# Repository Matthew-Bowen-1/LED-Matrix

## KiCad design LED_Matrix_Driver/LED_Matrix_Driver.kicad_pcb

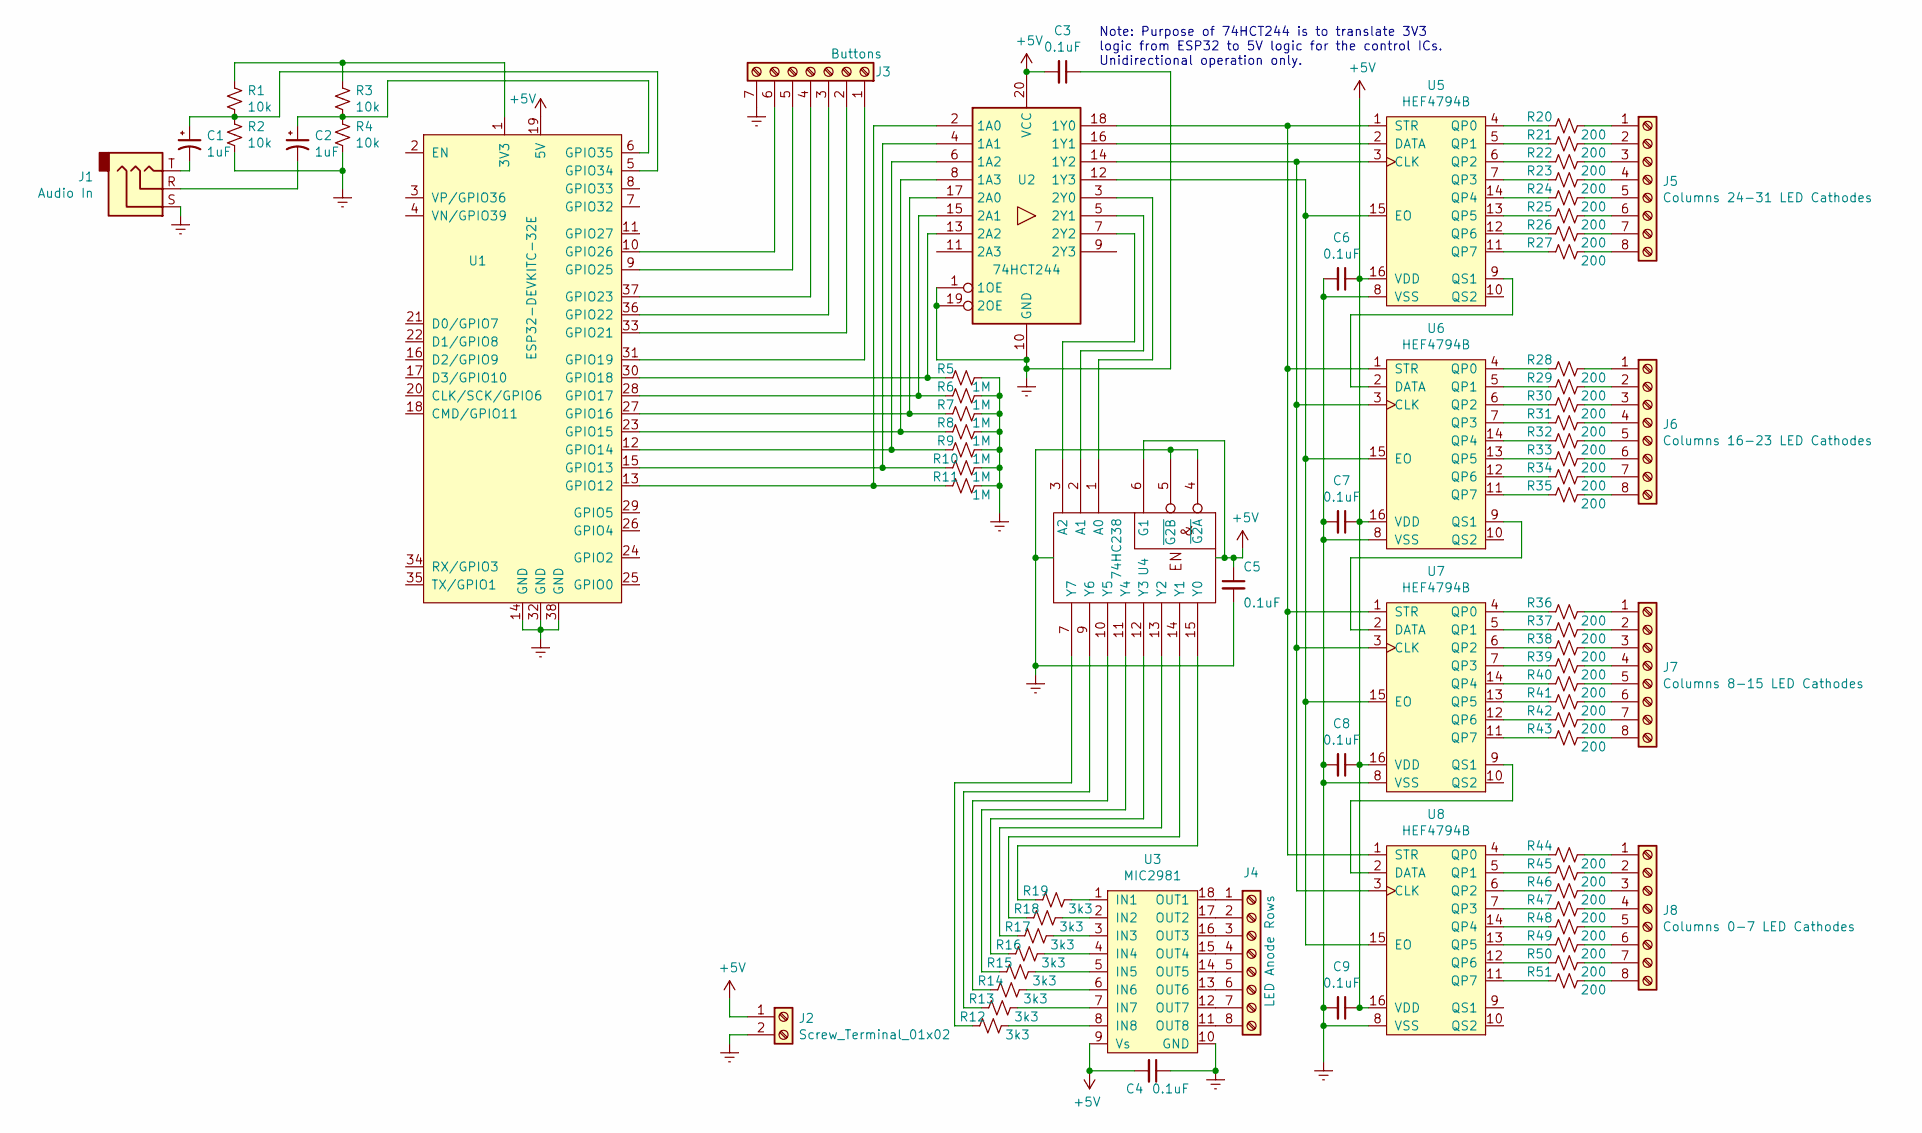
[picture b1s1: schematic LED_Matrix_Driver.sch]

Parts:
C1, C2: 1uF; CP_Radial_D4.0mm_P2.00mm
C3, C4, C5, C6, C7, C8, C9: 0.1uF; C_Rect_L7.0mm_W2.0mm_P5.00mm
J1: Audio In; Custom_Pin_Header_3
J2: Screw_Terminal_01x02; TerminalBlock_4Ucon_1x02_P3.50mm_Horizontal
J3: Buttons; Custom_Pin_Header_7
J4: LED Anode Rows; TerminalBlock_Phoenix_MKDS-1,5-8-5.08_1x08_P5.08mm_Horizont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
J5: Columns 24-31 LED Cathodes; TerminalBlock_Phoenix_MKDS-1,5-8-5.08_1x08_P5.08mm_Horizont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
J6: Columns 16-23 LED Cathodes; TerminalBlock_Phoenix_MKDS-1,5-8-5.08_1x08_P5.08mm_Horizont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
J7: Columns 8-15 LED Cathodes; TerminalBlock_Phoenix_MKDS-1,5-8-5.08_1x08_P5.08mm_Horizont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
J8: Columns 0-7 LED Cathodes; TerminalBlock_Phoenix_MKDS-1,5-8-5.08_1x08_P5.08mm_Horizont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
R1, R2, R3, R4: 10k; R_Axial_DIN0207_L6.3mm_D2.5mm_P10.16mm_Horizontal
R5, R6, R7, R8, R9, R10, R11: 1M; R_Axial_DIN0207_L6.3mm_D2.5mm_P10.16mm_Horizontal
R12, R13, R14, R15, R16, R17, R18, R19: 3k3; R_Axial_DIN0207_L6.3mm_D2.5mm_P10.16mm_Horizontal
R20, R21, R22, R23, R24, R25, R26, R27, R28, R29, R30, R31, R32, R33, R34, R35, R36, R37, R38, R39, R40, R41, R42, R43, R44, R45, R46, R47, R48, R49, R50, R51: 200; R_Axial_DIN0207_L6.3mm_D2.5mm_P10.16mm_Horizontal
U1: ESP32-DEVKITC-32E; ESP32-DevkitC
U2: 74HCT244; DIP-20_W7.62mm_Socket
U3: MIC2981; DIP-18_W7.62mm_Socket
U4: 74HC238; DIP-16_W7.62mm_Socket
U5, U6, U7, U8: HEF4794B; DIP-16_W7.62mm_Socket

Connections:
+5V: C3.2, C4.2, C5.1, C6.1, C7.1, C8.1, C9.1, J2.1, U1.19 (5V), U2.20 (VCC), U3.9 (Vs), U4.6 (G1), U4.16 (VCC), U5.16 (VDD), U6.16 (VDD), U7.16 (VDD), U8.16 (VDD)
Earth: C3.1, C4.1, C5.2, C6.2, C7.2, C8.2, C9.2, J1.3, J1.S, J2.2, J3.7, R2.1, R4.1, R5.2, R6.2, R7.2, R8.2, R9.2, R10.2, R11.2, U1.14 (GND), U1.32 (GND), U1.38 (GND), U2.1 (1OE), U2.10 (GND), U2.19 (2OE), U3.10 (GND), U4.4 (~G2A), U4.5 (~G2B), U4.8 (GND), U5.8 (VSS), U6.8 (VSS), U7.8 (VSS), U8.8 (VSS)
unnamed: C1.1, R1.1, R2.2, U1.5 (GPIO34)
unnamed: C1.2, J1.1, J1.T
unnamed: C2.1, R3.1, R4.2, U1.6 (GPIO35)
unnamed: C2.2, J1.2, J1.R
unnamed: J3.1, U1.31 (GPIO19)
unnamed: J3.2, U1.33 (GPIO21)
unnamed: J3.3, U1.36 (GPIO22)
unnamed: J3.4, U1.37 (GPIO23)
unnamed: J3.5, U1.9 (GPIO25)
unnamed: J3.6, U1.10 (GPIO26)
unnamed: J4.1, U3.18 (OUT1)
unnamed: J4.2, U3.17 (OUT2)
unnamed: J4.3, U3.16 (OUT3)
unnamed: J4.4, U3.15 (OUT4)
unnamed: J4.5, U3.14 (OUT5)
unnamed: J4.6, U3.13 (OUT6)
unnamed: J4.7, U3.12 (OUT7)
unnamed: J4.8, U3.11 (OUT8)
unnamed: J5.1, R20.1
unnamed: J5.2, R21.1
unnamed: J5.3, R22.1
unnamed: J5.4, R23.1
unnamed: J5.5, R24.1
unnamed: J5.6, R25.1
unnamed: J5.7, R26.1
unnamed: J5.8, R27.1
unnamed: J6.1, R28.1
unnamed: J6.2, R29.1
unnamed: J6.3, R30.1
unnamed: J6.4, R31.1
unnamed: J6.5, R32.1
unnamed: J6.6, R33.1
unnamed: J6.7, R34.1
unnamed: J6.8, R35.1
unnamed: J7.1, R36.1
unnamed: J7.2, R37.1
unnamed: J7.3, R38.1
unnamed: J7.4, R39.1
unnamed: J7.5, R40.1
unnamed: J7.6, R41.1
unnamed: J7.7, R42.1
unnamed: J7.8, R43.1
unnamed: J8.1, R44.1
unnamed: J8.2, R45.1
unnamed: J8.3, R46.1
unnamed: J8.4, R47.1
unnamed: J8.5, R48.1
unnamed: J8.6, R49.1
unnamed: J8.7, R50.1
unnamed: J8.8, R51.1
unnamed: R1.2, R3.2, U1.1 (3V3)
unnamed: R5.1, U1.30 (GPIO18), U2.13 (2A2)
unnamed: R6.1, U1.28 (GPIO17), U2.15 (2A1)
unnamed: R7.1, U1.27 (GPIO16), U2.17 (2A0)
unnamed: R8.1, U1.23 (GPIO15), U2.8 (1A3)
unnamed: R9.1, U1.12 (GPIO14), U2.6 (1A2)
unnamed: R10.1, U1.15 (GPIO13), U2.4 (1A1)
unnamed: R11.1, U1.13 (GPIO12), U2.2 (1A0)
unnamed: R12.1, U3.8 (IN8)
unnamed: R12.2, U4.7 (Y7)
unnamed: R13.1, U3.7 (IN7)
unnamed: R13.2, U4.9 (Y6)
unnamed: R14.1, U3.6 (IN6)
unnamed: R14.2, U4.10 (Y5)
unnamed: R15.1, U3.5 (IN5)
unnamed: R15.2, U4.11 (Y4)
unnamed: R16.1, U3.4 (IN4)
unnamed: R16.2, U4.12 (Y3)
unnamed: R17.1, U3.3 (IN3)
unnamed: R17.2, U4.13 (Y2)
unnamed: R18.1, U3.2 (IN2)
unnamed: R18.2, U4.14 (Y1)
unnamed: R19.1, U3.1 (IN1)
unnamed: R19.2, U4.15 (Y0)
unnamed: R20.2, U5.4 (QP0)
unnamed: R21.2, U5.5 (QP1)
unnamed: R22.2, U5.6 (QP2)
unnamed: R23.2, U5.7 (QP3)
unnamed: R24.2, U5.14 (QP4)
unnamed: R25.2, U5.13 (QP5)
unnamed: R26.2, U5.12 (QP6)
unnamed: R27.2, U5.11 (QP7)
unnamed: R28.2, U6.4 (QP0)
unnamed: R29.2, U6.5 (QP1)
unnamed: R30.2, U6.6 (QP2)
unnamed: R31.2, U6.7 (QP3)
unnamed: R32.2, U6.14 (QP4)
unnamed: R33.2, U6.13 (QP5)
unnamed: R34.2, U6.12 (QP6)
unnamed: R35.2, U6.11 (QP7)
unnamed: R36.2, U7.4 (QP0)
unnamed: R37.2, U7.5 (QP1)
unnamed: R38.2, U7.6 (QP2)
unnamed: R39.2, U7.7 (QP3)
unnamed: R40.2, U7.14 (QP4)
unnamed: R41.2, U7.13 (QP5)
unnamed: R42.2, U7.12 (QP6)
unnamed: R43.2, U7.11 (QP7)
unnamed: R44.2, U8.4 (QP0)
unnamed: R45.2, U8.5 (QP1)
unnamed: R46.2, U8.6 (QP2)
unnamed: R47.2, U8.7 (QP3)
unnamed: R48.2, U8.14 (QP4)
unnamed: R49.2, U8.13 (QP5)
unnamed: R50.2, U8.12 (QP6)
unnamed: R51.2, U8.11 (QP7)
unnamed: U2.3 (2Y0), U4.1 (A0)
unnamed: U2.5 (2Y1), U4.2 (A1)
unnamed: U2.7 (2Y2), U4.3 (A2)
unnamed: U2.12 (1Y3), U5.15 (EO), U6.15 (EO), U7.15 (EO), U8.15 (EO)
unnamed: U2.14 (1Y2), U5.3 (CLK), U6.3 (CLK), U7.3 (CLK), U8.3 (CLK)
unnamed: U2.16 (1Y1), U5.2 (DATA)
unnamed: U2.18 (1Y0), U5.1 (STR), U6.1 (STR), U7.1 (STR), U8.1 (STR)
unnamed: U5.9 (QS1), U6.2 (DATA)
unnamed: U6.9 (QS1), U7.2 (DATA)
unnamed: U7.9 (QS1), U8.2 (DATA)

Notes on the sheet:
Note: Purpose of 74HCT244 is to translate 3V3 logic from ESP32 to 5V logic for the control ICs. Unidirectional operation only.

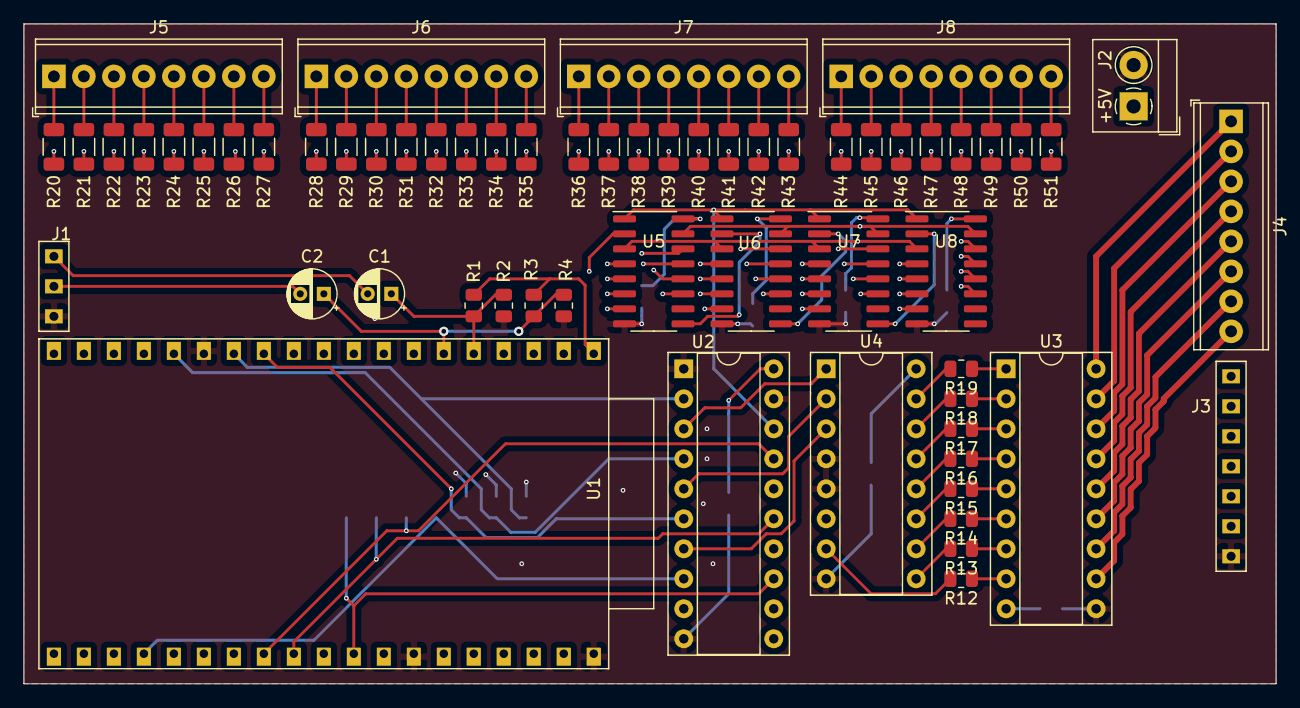
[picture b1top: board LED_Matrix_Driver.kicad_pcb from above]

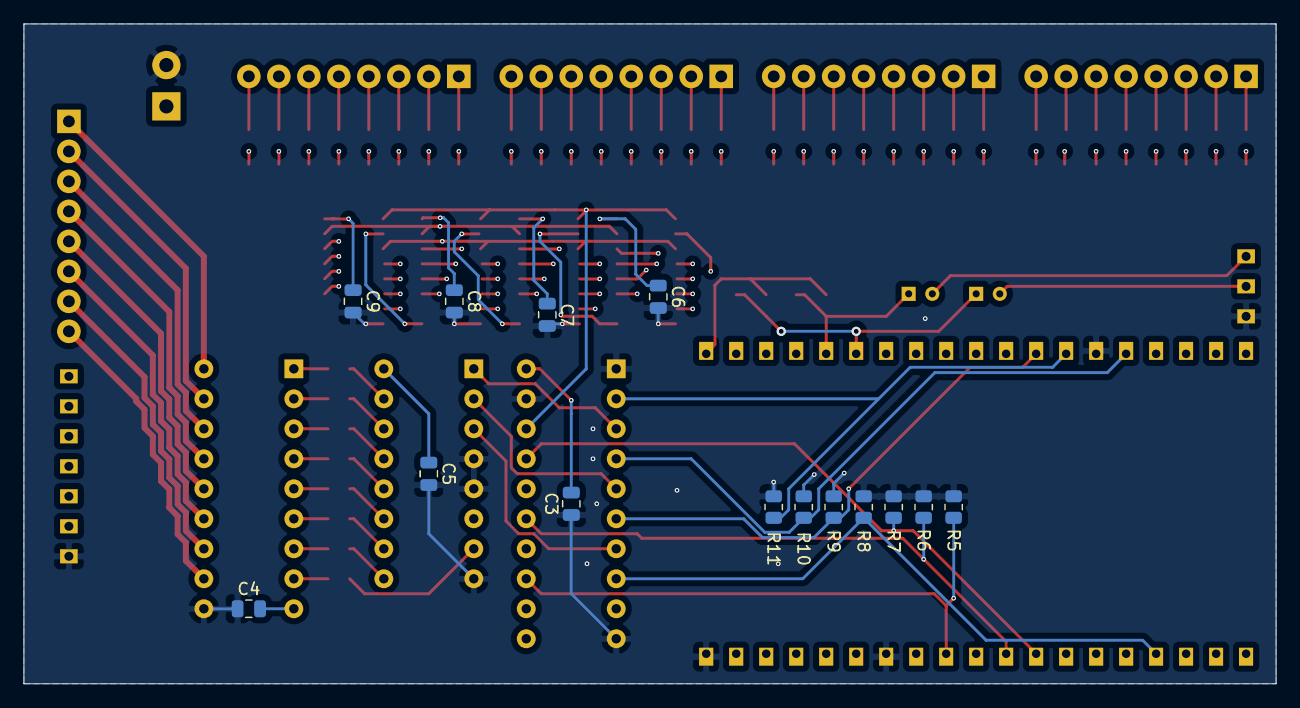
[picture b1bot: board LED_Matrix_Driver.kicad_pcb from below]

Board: 6 copper layers, 106.0 x 55.9 mm, 76 parts (14 on the bottom side), 118 nets.

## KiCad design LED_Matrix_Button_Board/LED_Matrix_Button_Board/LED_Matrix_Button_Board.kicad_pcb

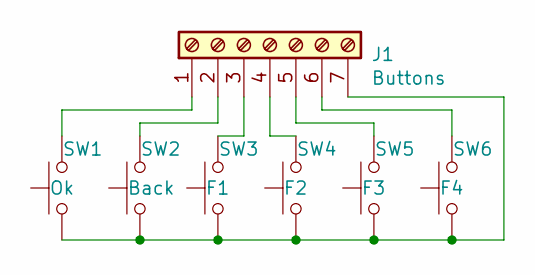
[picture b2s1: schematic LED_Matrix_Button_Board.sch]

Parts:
J1: Buttons; Custom_Pin_Header
SW1: Ok; SW_PUSH_6mm_H4.3mm
SW2: Back; SW_PUSH_6mm_H4.3mm
SW3: F1; SW_PUSH_6mm_H4.3mm
SW4: F2; SW_PUSH_6mm_H4.3mm
SW5: F3; SW_PUSH_6mm_H4.3mm
SW6: F4; SW_PUSH_6mm_H4.3mm

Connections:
unnamed: J1.1, SW1.2
unnamed: J1.2, SW2.2
unnamed: J1.3, SW3.2
unnamed: J1.4, SW4.2
unnamed: J1.5, SW5.2
unnamed: J1.6, SW6.2
unnamed: J1.7, SW1.1, SW2.1, SW3.1, SW4.1, SW5.1, SW6.1

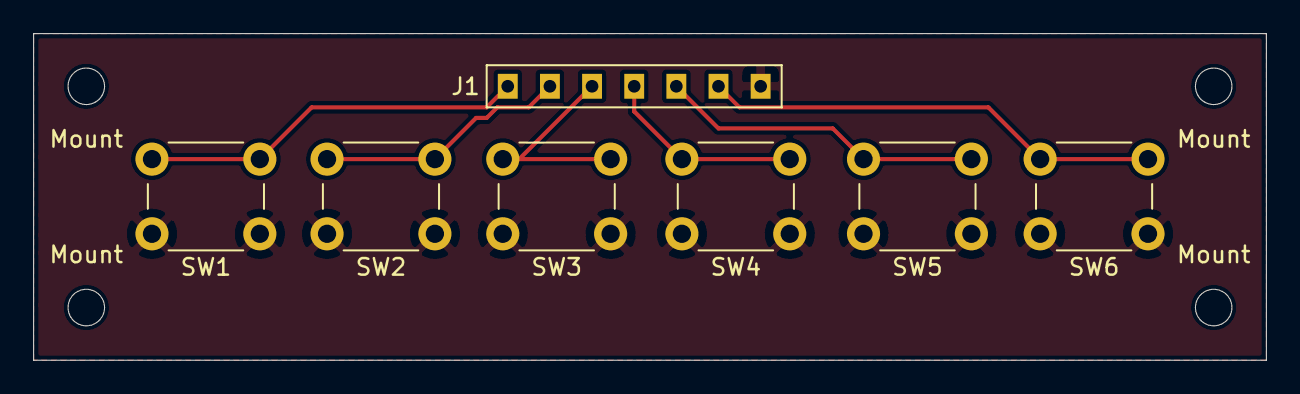
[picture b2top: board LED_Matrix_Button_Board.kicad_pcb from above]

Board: 2 copper layers, 74.3 x 19.7 mm, 11 parts (0 on the bottom side), 7 nets.

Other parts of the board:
Mount: MountingHole_2.2mm_M2
Mount#2, Mount#3, Mount#4: MountingHole_2.2mm_M2

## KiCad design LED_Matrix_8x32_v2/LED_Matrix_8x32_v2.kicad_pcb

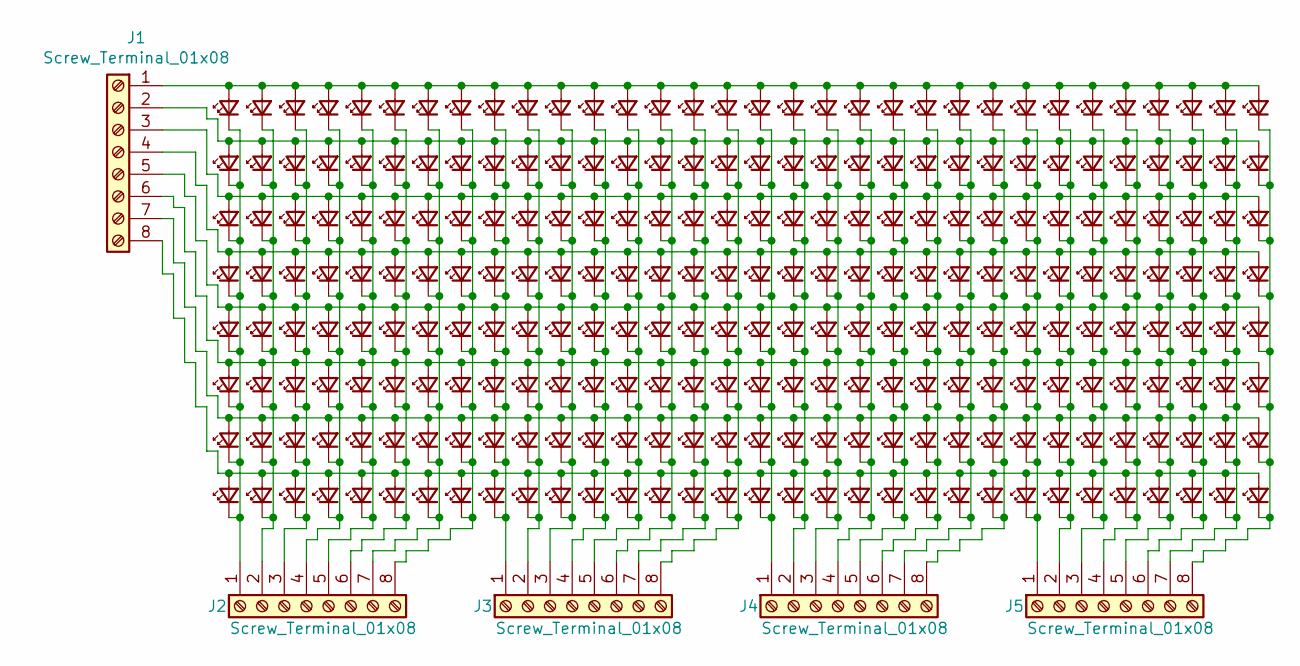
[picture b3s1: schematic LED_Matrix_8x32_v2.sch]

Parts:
D1, D2, D3, D4, D5, D6, D7, D8, D9, D10, D11, D12, D13, D14, D15, D16, D17, D18, D19, D20, D21, D22, D23, D24, D25, D26, D27, D28, D29, D30, D31, D32, D33, D34, D35, D36, D37, D38, D39, D40, D41, D42, D43, D44, D45, D46, D47, D48, D49, D50, D51, D52, D53, D54, D55, D56, D57, D58, D59, D60, D61, D62, D63, D64, D65, D66, D67, D68, D69, D70, D71, D72, D73, D74, D75, D76, D77, D78, D79, D80, D81, D82, D83, D84, D85, D86, D87, D88, D89, D90, D91, D92, D93, D94, D95, D96, D97, D98, D99, D100, D101, D102, D103, D104, D105, D106, D107, D108, D109, D110, D111, D112, D113, D114, D115, D116, D117, D118, D119, D120, D121, D122, D123, D124, D125, D126, D127, D128, D129, D130, D131, D132, D133, D134, D135, D136, D137, D138, D139, D140, D141, D142, D143, D144, D145, D146, D147, D148, D149, D150, D151, D152, D153, D154, D155, D156, D157, D158, D159, D160, D161, D162, D163, D164, D165, D166, D167, D168, D169, D170, D171, D172, D173, D174, D175, D176, D177, D178, D179, D180, D181, D182, D183, D184, D185, D186, D187, D188, D189, D190, D191, D192, D193, D194, D195, D196, D197, D198, D199, D200, D201, D202, D203, D204, D205, D206, D207, D208, D209, D210, D211, D212, D213, D214, D215, D216, D217, D218, D219, D220, D221, D222, D223, D224, D225, D226, D227, D228, D229, D230, D231, D232, D233, D234, D235, D236, D237, D238, D239, D240, D241, D242, D243, D244, D245, D246, D247, D248, D249, D250, D251, D252, D253, D254, D255, D256: LED; LED_D5.0mm_Silk_Moved
J1, J2, J3, J4, J5: Screw_Terminal_01x08; TerminalBlock_4Ucon_1x08_P3.50mm_Horizontal

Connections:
unnamed 0: D1.1 (K), D2.1 (K), D3.1 (K), D4.1 (K), D5.1 (K), D6.1 (K), D7.1 (K), D8.1 (K), J2.1; also elsewhere on the board
unnamed 1: D1.2 (A), D9.2 (A), D17.2 (A), D25.2 (A), D33.2 (A), D41.2 (A), D49.2 (A), D57.2 (A), D65.2 (A), D73.2 (A), D81.2 (A), D89.2 (A), D97.2 (A), D105.2 (A), D113.2 (A), D121.2 (A), D129.2 (A), D137.2 (A), D145.2 (A), D153.2 (A), D161.2 (A), D169.2 (A), D177.2 (A), D185.2 (A), D193.2 (A), D201.2 (A), D209.2 (A), D217.2 (A), D225.2 (A), D233.2 (A), D241.2 (A), D249.2 (A), J1.1; also elsewhere on the board
unnamed 2: D9.1 (K), D10.1 (K), D11.1 (K), D12.1 (K), D13.1 (K), D14.1 (K), D15.1 (K), D16.1 (K), J2.2; also elsewhere on the board
unnamed 3: D2.2 (A), D10.2 (A), D18.2 (A), D26.2 (A), D34.2 (A), D42.2 (A), D50.2 (A), D58.2 (A), D66.2 (A), D74.2 (A), D82.2 (A), D90.2 (A), D98.2 (A), D106.2 (A), D114.2 (A), D122.2 (A), D130.2 (A), D138.2 (A), D146.2 (A), D154.2 (A), D162.2 (A), D170.2 (A), D178.2 (A), D186.2 (A), D194.2 (A), D202.2 (A), D210.2 (A), D218.2 (A), D226.2 (A), D234.2 (A), D242.2 (A), D250.2 (A), J1.2; also elsewhere on the board
unnamed 4: D17.1 (K), D18.1 (K), D19.1 (K), D20.1 (K), D21.1 (K), D22.1 (K), D23.1 (K), D24.1 (K), J2.3; also elsewhere on the board
unnamed 5: D25.1 (K), D26.1 (K), D27.1 (K), D28.1 (K), D29.1 (K), D30.1 (K), D31.1 (K), D32.1 (K), J2.4; also elsewhere on the board
unnamed 6: D33.1 (K), D34.1 (K), D35.1 (K), D36.1 (K), D37.1 (K), D38.1 (K), D39.1 (K), D40.1 (K), J2.5; also elsewhere on the board
unnamed 7: D41.1 (K), D42.1 (K), D43.1 (K), D44.1 (K), D45.1 (K), D46.1 (K), D47.1 (K), D48.1 (K), J2.6; also elsewhere on the board
unnamed 8: D49.1 (K), D50.1 (K), D51.1 (K), D52.1 (K), D53.1 (K), D54.1 (K), D55.1 (K), D56.1 (K), J2.7; also elsewhere on the board
unnamed 9: D57.1 (K), D58.1 (K), D59.1 (K), D60.1 (K), D61.1 (K), D62.1 (K), D63.1 (K), D64.1 (K), J2.8; also elsewhere on the board
unnamed 10: D65.1 (K), D66.1 (K), D67.1 (K), D68.1 (K), D69.1 (K), D70.1 (K), D71.1 (K), D72.1 (K), J3.1; also elsewhere on the board
unnamed 11: D73.1 (K), D74.1 (K), D75.1 (K), D76.1 (K), D77.1 (K), D78.1 (K), D79.1 (K), D80.1 (K), J3.2; also elsewhere on the board
unnamed 12: D81.1 (K), D82.1 (K), D83.1 (K), D84.1 (K), D85.1 (K), D86.1 (K), D87.1 (K), D88.1 (K), J3.3; also elsewhere on the board
unnamed 13: D89.1 (K), D90.1 (K), D91.1 (K), D92.1 (K), D93.1 (K), D94.1 (K), D95.1 (K), D96.1 (K), J3.4; also elsewhere on the board
unnamed 14: D97.1 (K), D98.1 (K), D99.1 (K), D100.1 (K), D101.1 (K), D102.1 (K), D103.1 (K), D104.1 (K), J3.5; also elsewhere on the board
unnamed 15: D4.2 (A), D12.2 (A), D20.2 (A), D28.2 (A), D36.2 (A), D44.2 (A), D52.2 (A), D60.2 (A), D68.2 (A), D76.2 (A), D84.2 (A), D92.2 (A), D100.2 (A), D108.2 (A), D116.2 (A), D124.2 (A), D132.2 (A), D140.2 (A), D148.2 (A), D156.2 (A), D164.2 (A), D172.2 (A), D180.2 (A), D188.2 (A), D196.2 (A), D204.2 (A), D212.2 (A), D220.2 (A), D228.2 (A), D236.2 (A), D244.2 (A), D252.2 (A), J1.4; also elsewhere on the board
unnamed 16: D5.2 (A), D13.2 (A), D21.2 (A), D29.2 (A), D37.2 (A), D45.2 (A), D53.2 (A), D61.2 (A), D69.2 (A), D77.2 (A), D85.2 (A), D93.2 (A), D101.2 (A), D109.2 (A), D117.2 (A), D125.2 (A), D133.2 (A), D141.2 (A), D149.2 (A), D157.2 (A), D165.2 (A), D173.2 (A), D181.2 (A), D189.2 (A), D197.2 (A), D205.2 (A), D213.2 (A), D221.2 (A), D229.2 (A), D237.2 (A), D245.2 (A), D253.2 (A), J1.5; also elsewhere on the board
unnamed 17: D6.2 (A), D14.2 (A), D22.2 (A), D30.2 (A), D38.2 (A), D46.2 (A), D54.2 (A), D62.2 (A), D70.2 (A), D78.2 (A), D86.2 (A), D94.2 (A), D102.2 (A), D110.2 (A), D118.2 (A), D126.2 (A), D134.2 (A), D142.2 (A), D150.2 (A), D158.2 (A), D166.2 (A), D174.2 (A), D182.2 (A), D190.2 (A), D198.2 (A), D206.2 (A), D214.2 (A), D222.2 (A), D230.2 (A), D238.2 (A), D246.2 (A), D254.2 (A), J1.6; also elsewhere on the board
unnamed 18: D7.2 (A), D15.2 (A), D23.2 (A), D31.2 (A), D39.2 (A), D47.2 (A), D55.2 (A), D63.2 (A), D71.2 (A), D79.2 (A), D87.2 (A), D95.2 (A), D103.2 (A), D111.2 (A), D119.2 (A), D127.2 (A), D135.2 (A), D143.2 (A), D151.2 (A), D159.2 (A), D167.2 (A), D175.2 (A), D183.2 (A), D191.2 (A), D199.2 (A), D207.2 (A), D215.2 (A), D223.2 (A), D231.2 (A), D239.2 (A), D247.2 (A), D255.2 (A), J1.7; also elsewhere on the board
unnamed 19: D8.2 (A), D16.2 (A), D24.2 (A), D32.2 (A), D40.2 (A), D48.2 (A), D56.2 (A), D64.2 (A), D72.2 (A), D80.2 (A), D88.2 (A), D96.2 (A), D104.2 (A), D112.2 (A), D120.2 (A), D128.2 (A), D136.2 (A), D144.2 (A), D152.2 (A), D160.2 (A), D168.2 (A), D176.2 (A), D184.2 (A), D192.2 (A), D200.2 (A), D208.2 (A), D216.2 (A), D224.2 (A), D232.2 (A), D240.2 (A), D248.2 (A), D256.2 (A), J1.8; also elsewhere on the board
unnamed 20: D105.1 (K), D106.1 (K), D107.1 (K), D108.1 (K), D109.1 (K), D110.1 (K), D111.1 (K), D112.1 (K), J3.6; also elsewhere on the board
unnamed 21: D3.2 (A), D11.2 (A), D19.2 (A), D27.2 (A), D35.2 (A), D43.2 (A), D51.2 (A), D59.2 (A), D67.2 (A), D75.2 (A), D83.2 (A), D91.2 (A), D99.2 (A), D107.2 (A), D115.2 (A), D123.2 (A), D131.2 (A), D139.2 (A), D147.2 (A), D155.2 (A), D163.2 (A), D171.2 (A), D179.2 (A), D187.2 (A), D195.2 (A), D203.2 (A), D211.2 (A), D219.2 (A), D227.2 (A), D235.2 (A), D243.2 (A), D251.2 (A), J1.3; also elsewhere on the board
unnamed 22: D113.1 (K), D114.1 (K), D115.1 (K), D116.1 (K), D117.1 (K), D118.1 (K), D119.1 (K), D120.1 (K), J3.7; also elsewhere on the board
unnamed 23: D121.1 (K), D122.1 (K), D123.1 (K), D124.1 (K), D125.1 (K), D126.1 (K), D127.1 (K), D128.1 (K), J3.8; also elsewhere on the board
unnamed 24: D129.1 (K), D130.1 (K), D131.1 (K), D132.1 (K), D133.1 (K), D134.1 (K), D135.1 (K), D136.1 (K), J4.1; also elsewhere on the board
unnamed 25: D137.1 (K), D138.1 (K), D139.1 (K), D140.1 (K), D141.1 (K), D142.1 (K), D143.1 (K), D144.1 (K), J4.2; also elsewhere on the board
unnamed 26: D145.1 (K), D146.1 (K), D147.1 (K), D148.1 (K), D149.1 (K), D150.1 (K), D151.1 (K), D152.1 (K), J4.3; also elsewhere on the board
unnamed 27: D153.1 (K), D154.1 (K), D155.1 (K), D156.1 (K), D157.1 (K), D158.1 (K), D159.1 (K), D160.1 (K), J4.4; also elsewhere on the board
unnamed 28: D161.1 (K), D162.1 (K), D163.1 (K), D164.1 (K), D165.1 (K), D166.1 (K), D167.1 (K), D168.1 (K), J4.5; also elsewhere on the board
unnamed 29: D169.1 (K), D170.1 (K), D171.1 (K), D172.1 (K), D173.1 (K), D174.1 (K), D175.1 (K), D176.1 (K), J4.6; also elsewhere on the board
unnamed 30: D177.1 (K), D178.1 (K), D179.1 (K), D180.1 (K), D181.1 (K), D182.1 (K), D183.1 (K), D184.1 (K), J4.7; also elsewhere on the board
unnamed 31: D185.1 (K), D186.1 (K), D187.1 (K), D188.1 (K), D189.1 (K), D190.1 (K), D191.1 (K), D192.1 (K), J4.8; also elsewhere on the board
unnamed 32: D193.1 (K), D194.1 (K), D195.1 (K), D196.1 (K), D197.1 (K), D198.1 (K), D199.1 (K), D200.1 (K), J5.1; also elsewhere on the board
unnamed 33: D201.1 (K), D202.1 (K), D203.1 (K), D204.1 (K), D205.1 (K), D206.1 (K), D207.1 (K), D208.1 (K), J5.2; also elsewhere on the board
unnamed 34: D209.1 (K), D210.1 (K), D211.1 (K), D212.1 (K), D213.1 (K), D214.1 (K), D215.1 (K), D216.1 (K), J5.3; also elsewhere on the board
unnamed 35: D217.1 (K), D218.1 (K), D219.1 (K), D220.1 (K), D221.1 (K), D222.1 (K), D223.1 (K), D224.1 (K), J5.4; also elsewhere on the board
unnamed 36: D225.1 (K), D226.1 (K), D227.1 (K), D228.1 (K), D229.1 (K), D230.1 (K), D231.1 (K), D232.1 (K), J5.5; also elsewhere on the board
unnamed 37: D233.1 (K), D234.1 (K), D235.1 (K), D236.1 (K), D237.1 (K), D238.1 (K), D239.1 (K), D240.1 (K), J5.6; also elsewhere on the board
unnamed 38: D241.1 (K), D242.1 (K), D243.1 (K), D244.1 (K), D245.1 (K), D246.1 (K), D247.1 (K), D248.1 (K), J5.7; also elsewhere on the board
unnamed 39: D249.1 (K), D250.1 (K), D251.1 (K), D252.1 (K), D253.1 (K), D254.1 (K), D255.1 (K), D256.1 (K), J5.8; also elsewhere on the board

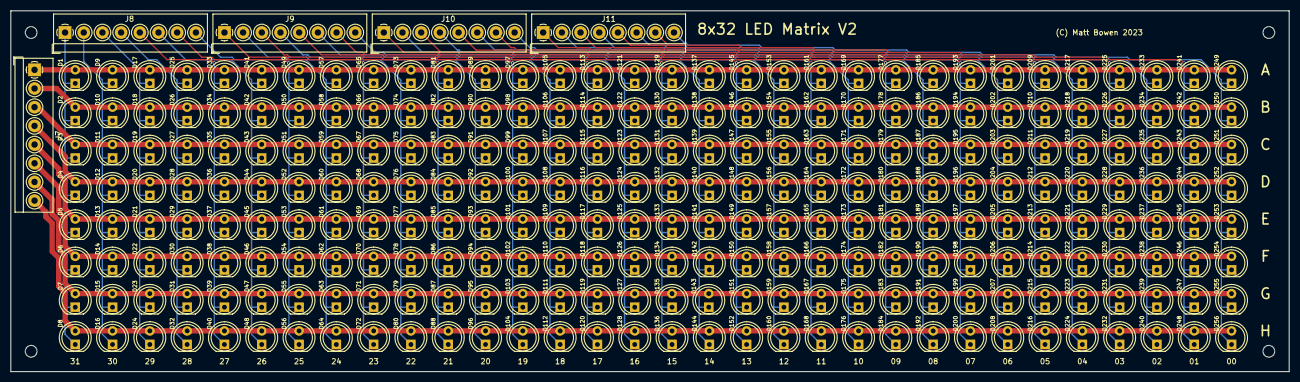
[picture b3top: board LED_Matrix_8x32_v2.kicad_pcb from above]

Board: 2 copper layers, 239.4 x 67.6 mm, 261 parts (0 on the bottom side), 40 nets.

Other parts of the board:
J7, J8, J9, J10, J11: Screw_Terminal_01x08; TerminalBlock_4Ucon_1x08_P3.50mm_Horizontal

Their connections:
unnamed 0: J8.1; also elsewhere on the board
unnamed 1: J7.1; also elsewhere on the board
unnamed 2: J8.2; also elsewhere on the board
unnamed 3: J7.2; also elsewhere on the board
unnamed 4: J8.3; also elsewhere on the board
unnamed 5: J8.4; also elsewhere on the board
unnamed 6: J8.5; also elsewhere on the board
unnamed 7: J8.6; also elsewhere on the board
unnamed 8: J8.7; also elsewhere on the board
unnamed 9: J8.8; also elsewhere on the board
unnamed 10: J9.1; also elsewhere on the board
unnamed 11: J9.2; also elsewhere on the board
unnamed 12: J9.3; also elsewhere on the board
unnamed 13: J9.4; also elsewhere on the board
unnamed 14: J9.5; also elsewhere on the board
unnamed 15: J7.4; also elsewhere on the board
unnamed 16: J7.5; also elsewhere on the board
unnamed 17: J7.6; also elsewhere on the board
unnamed 18: J7.7; also elsewhere on the board
unnamed 19: J7.8; also elsewhere on the board
unnamed 20: J9.6; also elsewhere on the board
unnamed 21: J7.3; also elsewhere on the board
unnamed 22: J9.7; also elsewhere on the board
unnamed 23: J9.8; also elsewhere on the board
unnamed 24: J10.1; also elsewhere on the board
unnamed 25: J10.2; also elsewhere on the board
unnamed 26: J10.3; also elsewhere on the board
unnamed 27: J10.4; also elsewhere on the board
unnamed 28: J10.5; also elsewhere on the board
unnamed 29: J10.6; also elsewhere on the board
unnamed 30: J10.7; also elsewhere on the board
unnamed 31: J10.8; also elsewhere on the board
unnamed 32: J11.1; also elsewhere on the board
unnamed 33: J11.2; also elsewhere on the board
unnamed 34: J11.3; also elsewhere on the board
unnamed 35: J11.4; also elsewhere on the board
unnamed 36: J11.5; also elsewhere on the board
unnamed 37: J11.6; also elsewhere on the board
unnamed 38: J11.7; also elsewhere on the board
unnamed 39: J11.8; also elsewhere on the board

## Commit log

2023-10-04 Initialized Repository
2023-10-04 First test commit of ESP32 branch
2023-10-11 Created symbol for ESP32 Devkit and added it to the schematic
2023-10-16 Added Reference files
2023-11-08 Big Commit:
    - Hardware files are complete
    - Final hardware iteration until further notice.
    - Generated new firmware project with Platform.io in VSCode
    - Will use git more with this
2023-11-09 Created a few core functions
2023-11-10 Created global "Image" array. Currently an array of size 8x32. Does not allow for image to be manipulated properly
2023-11-10 combined setPinLow and setPinHigh into setPin
2023-11-13 Created LEDMatrix library. Moved relevant functions to LEDMatrix.cpp
    Next task is to create a method of audio input for use of the display as
    a spectrum analyzer.
2023-11-13 Added a few comments
2023-11-15 Created LEDMatrixText library and associated font
    Next task is to create scrollPrint function
2023-11-15 Updated the shift() function in LEDMatrix.cpp Now takes a frame delay amount as a parameter
2023-11-17 Created font for LEDMatrixText Currently working on scrollPrint() and shiftChar() functions
2023-11-20 Implemented LEDMatrixText library. Can now use scrollPrint() to print strings to the display.
2023-11-20 Made some minor tweaks to the PCB layout. Will not physically implement them until later date.
2023-11-20 Implemented scrollPrintInt function to print signed integers
2023-11-24 Forgot to free memory after calling calloc in scrollPrintInt
2023-11-24 Fixed a big with scrollPrintInt where printing 0 would cause it to loop indefinitely
2023-11-24 Added scrollPrintUint to LEDMatrixText
2023-11-24 Created a new PCB layout for LEDMatrixDriver board
    - More compact
    - Removed unused capacitors
2023-11-27 Slight change to main.cpp for demonstartion purposes only
2023-11-27 Started work on including an ATmega328P in the schematic
2023-11-27 Fixed continuity errors in master branch
2023-11-27 More timeline fixes for the master branch
2023-11-29 Implemented staticPrint and staticChar functions
2023-11-29 Minor testing of the staticPrint function
2023-11-29 Minor tweaks so that shift() no longer relies on infinite while loops
2023-11-29 Created Timekeeper library Also changed initializeDisplay slightly to require the user to specify which hardware timer to use
2023-11-30 Implemented a clock mode. Requires that the updateClockFace function be called within the loop. This is a work in progress. I cannot get it to work when called from the clock's ISR
2023-11-30 Modified design to include decoupling capacitors. PCB is now 4 layers with power and ground planes
2023-11-30 Implemented functions within Timekeeper.cpp
    Also included new shiftIn function to scroll images onto the display
2023-11-30 Clock mode adjustments
2023-12-04 Reset the time. No important changes
2023-12-04 Changed clock timer operation to include half seconds for the purpose of blinking the seconds LED every second
    Modified updateClockFace() to scrollPrint a message on the hour and half hour.
2023-12-04 Added half hour message
2023-12-04 Fixed the half hour message
2023-12-04 reset to proper time
2023-12-04 Added 6 push buttons to the PCB as well as 4 mounting holes
2023-12-06 Seconds are now displayed as a binary number under the time.
    Separated generateClockFaceString functionality from updateClockFace()
    added getNumberString to allow for printing the time as words instead of
    digits
2023-12-06 Updated the time
2023-12-06 Test for github to properly display my commit activity
2023-12-06 Git test for contributions
2023-12-06 Another github test
2023-12-06 Revert "Merge pull request #1 from Matthew-Bowen-1/ClockMode"
2023-12-06 Revert "Clock mode"
2023-12-06 small changes to timekeeper
2023-12-07 Revert "small changes to timekeeper"
2023-12-07 Changed the time
2023-12-08 Updated the PCB. Now includes solder points for a few buttons
2023-12-08 Updated Driver board to include sinlge header for all 6 buttons
    Created new daughter board to hold the buttons
2023-12-08 Added some text to the boards
2023-12-08 Minor change to timekeeper to change the blinking behavior of the half hourly messages
2023-12-12 Added audio input circuitry for potential audio applications
2023-12-12 Started work on 5mm LED 8x32 matrix board
2023-12-15 Created Gerber plots of new driver board design, button board, and new LED board As of 12/15/2023, all three PCBs have been submitted to JLCPCB for manufacturing.
2023-12-18 Modification of LED_Matrix_Driver to use SMD components
2023-12-18 Finished PCB design for board revision 1.1
